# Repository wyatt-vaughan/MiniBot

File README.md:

# MiniBot

A swarm robotics platform built around autonomous chess. The system runs 34 small
differential-drive robots across an 8x8 board, each independently localized and
coordinated by a central Python application running on a Raspberry Pi.

The design is general-purpose — chess is the primary use case, but the platform
works for any scenario requiring coordinated movement of many small autonomous
robots in a bounded space.

Per-bot hardware cost is approximately $4 excluding PCB.

---

## Table of Contents

1. [System Architecture](#system-architecture)
2. [Hardware](#hardware)
3. [Communication Pathways](#communication-pathways)
4. [Server-Bot Sync](#server-bot-sync)
5. [Localization](#localization)
6. [PCB and CAD](#pcb-and-cad)
7. [Firmware](#firmware)

---

## System Architecture

The system has three layers:

**Coordinator** is a Python/PyQt6 application running on a Raspberry Pi. It holds
board state, runs path planning, drives the GUI, and sends motion commands to the
Server over USB serial.

**Server** is an ESP32 on the motherboard. It acts as a wireless gateway: it receives
CSV commands from the Coordinator over USB serial, translates them to binary ESP-NOW
messages, and broadcasts them to the bots. It also drives the electromagnets used for
localization and collects ACK/NACK responses back up to the Coordinator.

**MiniBots** are the robots themselves. Each runs an ESP32-C3 with five concurrent
FreeRTOS tasks handling motion control, wireless communication, position estimation,
and battery management entirely onboard.

---

## Hardware

### MiniBot

| Component | Details |
|-----------|---------|
| MCU | ESP32-C3 (RISC-V, 2.4 GHz WiFi) |
| Motors | 2x PMO8-2 miniature stepper motors |
| Motor drivers | STSPIN220 |
| Magnetometer | MMC5633NJL (I2C) |
| Power | ~170 mAh LiPo |
| Chassis | Fully 3D printed; 2x M2x5mm bolts, 2x 7mm ID o-rings for tires |
| PCB | Custom 4-layer; fits in the base of the chassis |

### Server / Motherboard

| Component | Details |
|-----------|---------|
| MCU | ESP32-C3 (RISC-V, 2.4 GHz WiFi) |
| Electromagnets | Multiple, positioned at fixed known coordinates on the board |
| Interface | USB serial to Raspberry Pi |
| WiFi | Soft AP; bots connect on a dedicated channel |

The electromagnets fire in a timed sequence that the MiniBots detect with their
onboard magnetometers. This is the primary localization mechanism.

---

## Communication Pathways

```mermaid
flowchart TD
    subgraph Coordinator["Coordinator (Raspberry Pi)"]
        GUI["GUI / Path Planner"]
        SH["SerialHandler\n(QThread)"]
        GUI -->|MoveCommand list| SH
    end

    subgraph Server["Server (Motherboard ESP32)"]
        ST["SerialTask"]
        CT["CommunicatorTask"]
        ET["ElectromagnetTask"]
        ST -->|CommandMessage| CT
        CT -->|GUIStatus| ST
    end

    subgraph Bots["MiniBot #1 ... #34 (ESP32-C3)"]
        COMM["EspNowCommunicator"]
        KIN["KinematicsController"]
        PE["PositionEstimator"]
        COMM -->|MotionCommand| KIN
        COMM -->|sync time| PE
    end

    SH -->|"Serial CSV Commands"| ST
    ST -->|"Serial CSV Responses"| SH
    CT -->|"ESP-NOW\nbroadcast / unicast Commands"| COMM
    COMM -->|"ESP-NOW unicast\nACK / NACK"| CT
    ET -.->|"electromagnetic\nframe pulses"| PE
```

### CSV Protocol (Host to Server)

All messages are prefixed with `>`. The Server parses these and forwards the
appropriate ESP-NOW message to the targeted bot(s).

| Type | Direction | Format |
|------|-----------|--------|
| 0 | Host to ESP32 | `>0,{id},{mode},{duty1},{duty2}` -- motor test |
| 1 | Host to ESP32 | `>1,{id},{x},{y},{theta_rad},{duration_ms}` -- position command |
| 2 | Host to ESP32 | `>2,{id}` -- position request |
| 3 | ESP32 to Host | `>3,{id},{x},{y},{theta_rad},{timestamp_ms},{battery_v}` -- ACK |
| 4 | ESP32 to Host | `>4,{id},{err_type},{timestamp_ms}` -- NACK |
| 5 | Host to ESP32 | `>5,{id}` -- mag field request |
| 6 | ESP32 to Host | `>6,{id},{bx},{by},{bz},{timestamp_ms}` -- mag field response |
| 7 | Host to ESP32 | `>7` -- sync broadcast |
| 254 | Host to ESP32 | `>254,{0 or 1}` -- electromagnet enable/disable |
| 255 | Both | `>255` -- ping/pong |

Theta is transmitted in radians on the wire. The Coordinator converts internally;
all application-level code uses degrees.

### ESP-NOW Protocol (Server to MiniBots)

Binary packed structs defined in `ESPNowMessages.h` (Server) and
`messages_espnow.h` (MiniBot). Key message types: `PositionCommand`,
`MotTestCommand`, `PositionRequest`, `PosSync`, `AckMessage`, `NackMessage`,
`MagneticFieldRequest`, `MagneticFieldResponse`.

---

## Server-Bot Sync

Before a localization measurement can be taken, every MiniBot needs to know
precisely when the electromagnet frame will begin so it can timestamp its
magnetometer samples against a common reference.

**Initiating a sync** is triggered by the Coordinator sending a `>7` sync command.
The Server's `CommunicatorTask` handles it as follows:

1. A `PosSyncCommand` is broadcast to all bots. The message includes a timeout
   indicating how long the bots should stay awake listening for the frame.
2. After a short delay, the Server sends a rapid burst of `PosSync` pulses. Each
   carries a `next_frame_us` field indicating how many microseconds until the
   electromagnet frame starts.
3. The `ElectromagnetTask` fires the frame immediately after the burst completes.

**On each MiniBot**, when `PosSyncCommand` is received, `EspNowCommunicator` sets
a deadline and raises `waiting_for_pos_sync`. The ESP-NOW receive callback captures
a high-resolution timestamp the instant each `PosSync` pulse arrives, before any
further processing. The task keeps only the earliest-arriving pulse from the burst —
minimum latency gives the best timing accuracy. The estimated frame start is
`receive_time + next_frame_us` from that best pulse.

Once the deadline passes, the bot calls `PositionEstimator_SetSyncTime()` with the
estimated frame-start, then sends an ACK with a small random delay to spread
simultaneous responses from many bots. If no pulse arrived in time, it sends
`ERR_SYNC_TIMEOUT`.

**Radio duty cycling** is tied to sync health. After a successful sync, each bot
enables duty cycling to save power. If sync becomes stale, the radio reverts to
always-on so the Server can reach the bot to re-establish sync.

---

## Localization

The Server fires each electromagnet in sequence as part of a repeating frame. Each
slot has a brief forward and reverse pulse to produce a detectable field, with a
known timing offset between slots.

On each MiniBot, `PositionEstimator_SensorTask` reads the magnetometer
continuously. Once a valid sync time is set, it timestamps each sample relative to
the frame start and assigns samples to their electromagnet slot by timing alone.

Once a complete frame is collected, `PositionEstimator_CalcTask` performs
trilateration using the field strength readings from the closest electromagnets and
their known board positions. This yields an (x, y, orientation) estimate with a
confidence score, which is used to weight a low-pass filter before the result is
committed to the robot's true pose via `robot.setTruePose()`.

---

## PCB and CAD

Current board designs are in `pcbs/`:

- `pcbs/MiniBot_MainBoard/` -- MiniBot PCB (ESP32-C3, stepper drivers, magnetometer, LiPo charger)
- `pcbs/Server_Motherboard/` -- Motherboard (ESP32-C3, electromagnet drivers, connectors)

Gerber files are in the `GERBERS/` subdirectory of each board folder.

CAD (OnShape):
https://cad.onshape.com/documents/4f8eaef75458146767928ab5/w/f159d6d65b9091531e1ead34/e/13b51722310f27710438c727

---

## Firmware

Each firmware project has its own README with task breakdowns, key objects, and
build instructions.

- `firmware/MiniBot_Coordinator/` -- Python/PyQt6 host application
- `firmware/MiniBot_Server/` -- ESP32 motherboard firmware (PlatformIO)
- `firmware/MiniBot_StepperClient/` -- ESP32-C3 per-bot firmware (PlatformIO)

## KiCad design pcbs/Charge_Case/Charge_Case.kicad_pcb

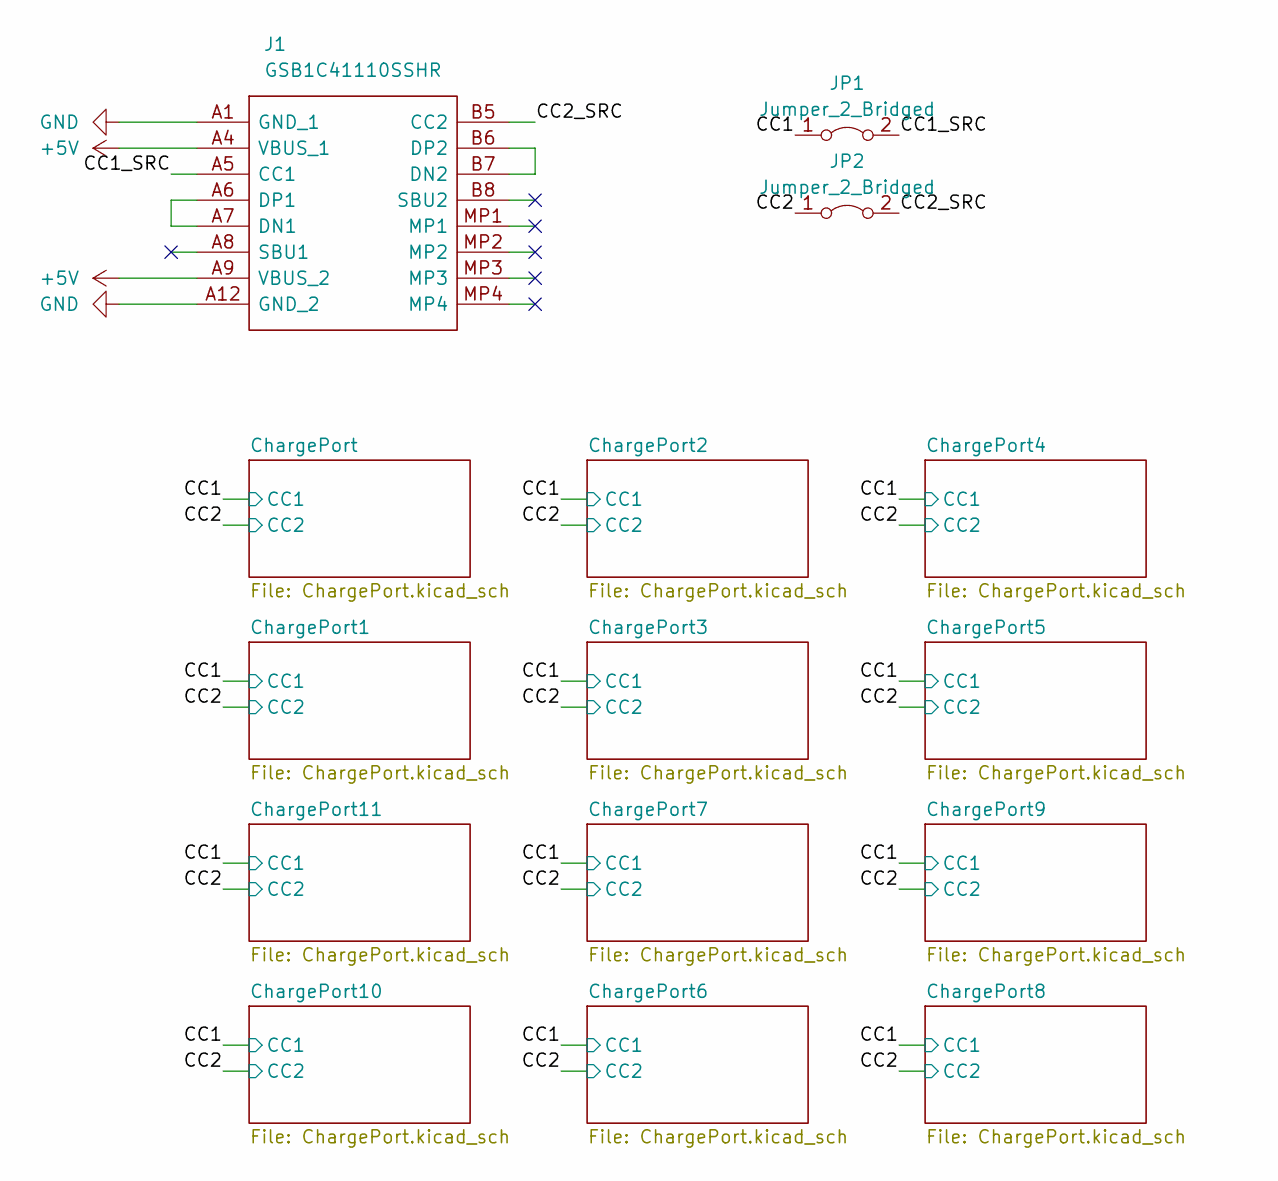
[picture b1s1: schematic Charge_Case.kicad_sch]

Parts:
J1: GSB1C41110SSHR; Manufacturer_Part_Number GSB1C41110SSHR
JP1, JP2: Jumper_2_Bridged; SolderJumper-2_P1.3mm_Bridged_RoundedPad1.0x1.5mm

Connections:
+5V: J1.A4 (VBUS_1), J1.A9 (VBUS_2); also elsewhere on the board
/CC1: JP1.1 (A); also elsewhere on the board
/CC1_SRC: J1.A5 (CC1), JP1.2 (B)
/CC2: JP2.1 (A); also elsewhere on the board
/CC2_SRC: J1.B5 (CC2), JP2.2 (B)
GND: J1.A1 (GND_1), J1.A12 (GND_2); also elsewhere on the board
unnamed: J1.A6 (DP1), J1.A7 (DN1)
unnamed: J1.B6 (DP2), J1.B7 (DN2)

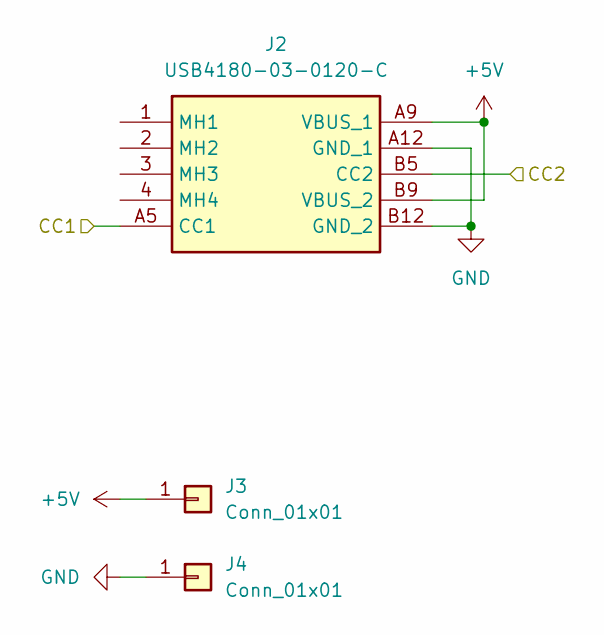
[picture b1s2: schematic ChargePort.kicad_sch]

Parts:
J2: USB4180-03-0120-C; USB4180030120C; Mouser Part Number 640-USB4180-03-0120C
J3, J4: Conn_01x01; TestPoint_THTPad_1.0x1.0mm_Drill0.5mm

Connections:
+5V: J2.A9 (VBUS_1), J2.B9 (VBUS_2), J3.1; also elsewhere on the board
/CC1: J2.A5 (CC1); also elsewhere on the board
/CC2: J2.B5 (CC2); also elsewhere on the board
GND: J2.A12 (GND_1), J2.B12 (GND_2), J4.1; also elsewhere on the board

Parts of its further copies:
J5, J8, J11, J14, J17, J20, J23, J26, J29, J32, J35: USB4180-03-0120-C; USB4180030120C; Mouser Part Number 640-USB4180-03-0120C
J6, J7, J9, J10, J12, J13, J15, J16, J18, J19, J21, J22, J24, J25, J27, J28, J30, J31, J33, J34, J36, J37: Conn_01x01; TestPoint_THTPad_1.0x1.0mm_Drill0.5mm

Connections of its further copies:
+5V: J5.A9 (VBUS_1), J5.B9 (VBUS_2), J6.1, J8.A9 (VBUS_1), J8.B9 (VBUS_2), J9.1, J11.A9 (VBUS_1), J11.B9 (VBUS_2), J12.1, J14.A9 (VBUS_1), J14.B9 (VBUS_2), J15.1, J17.A9 (VBUS_1), J17.B9 (VBUS_2), J18.1, J20.A9 (VBUS_1), J20.B9 (VBUS_2), J21.1, J23.A9 (VBUS_1), J23.B9 (VBUS_2), J24.1, J26.A9 (VBUS_1), J26.B9 (VBUS_2), J27.1, J29.A9 (VBUS_1), J29.B9 (VBUS_2), J30.1, J32.A9 (VBUS_1), J32.B9 (VBUS_2), J33.1, J35.A9 (VBUS_1), J35.B9 (VBUS_2), J36.1; also elsewhere on the board
/CC1: J5.A5 (CC1), J8.A5 (CC1), J11.A5 (CC1), J14.A5 (CC1), J17.A5 (CC1), J20.A5 (CC1), J23.A5 (CC1), J26.A5 (CC1), J29.A5 (CC1), J32.A5 (CC1), J35.A5 (CC1); also elsewhere on the board
/CC2: J5.B5 (CC2), J8.B5 (CC2), J11.B5 (CC2), J14.B5 (CC2), J17.B5 (CC2), J20.B5 (CC2), J23.B5 (CC2), J26.B5 (CC2), J29.B5 (CC2), J32.B5 (CC2), J35.B5 (CC2); also elsewhere on the board
GND: J5.A12 (GND_1), J5.B12 (GND_2), J7.1, J8.A12 (GND_1), J8.B12 (GND_2), J10.1, J11.A12 (GND_1), J11.B12 (GND_2), J13.1, J14.A12 (GND_1), J14.B12 (GND_2), J16.1, J17.A12 (GND_1), J17.B12 (GND_2), J19.1, J20.A12 (GND_1), J20.B12 (GND_2), J22.1, J23.A12 (GND_1), J23.B12 (GND_2), J25.1, J26.A12 (GND_1), J26.B12 (GND_2), J28.1, J29.A12 (GND_1), J29.B12 (GND_2), J31.1, J32.A12 (GND_1), J32.B12 (GND_2), J34.1, J35.A12 (GND_1), J35.B12 (GND_2), J37.1; also elsewhere on the board

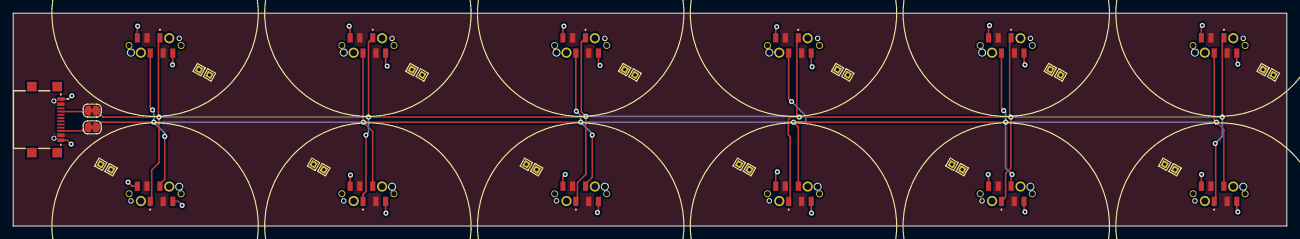
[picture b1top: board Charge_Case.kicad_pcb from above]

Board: 2 copper layers, 197.5 x 33.0 mm, 39 parts (0 on the bottom side), 8 nets.

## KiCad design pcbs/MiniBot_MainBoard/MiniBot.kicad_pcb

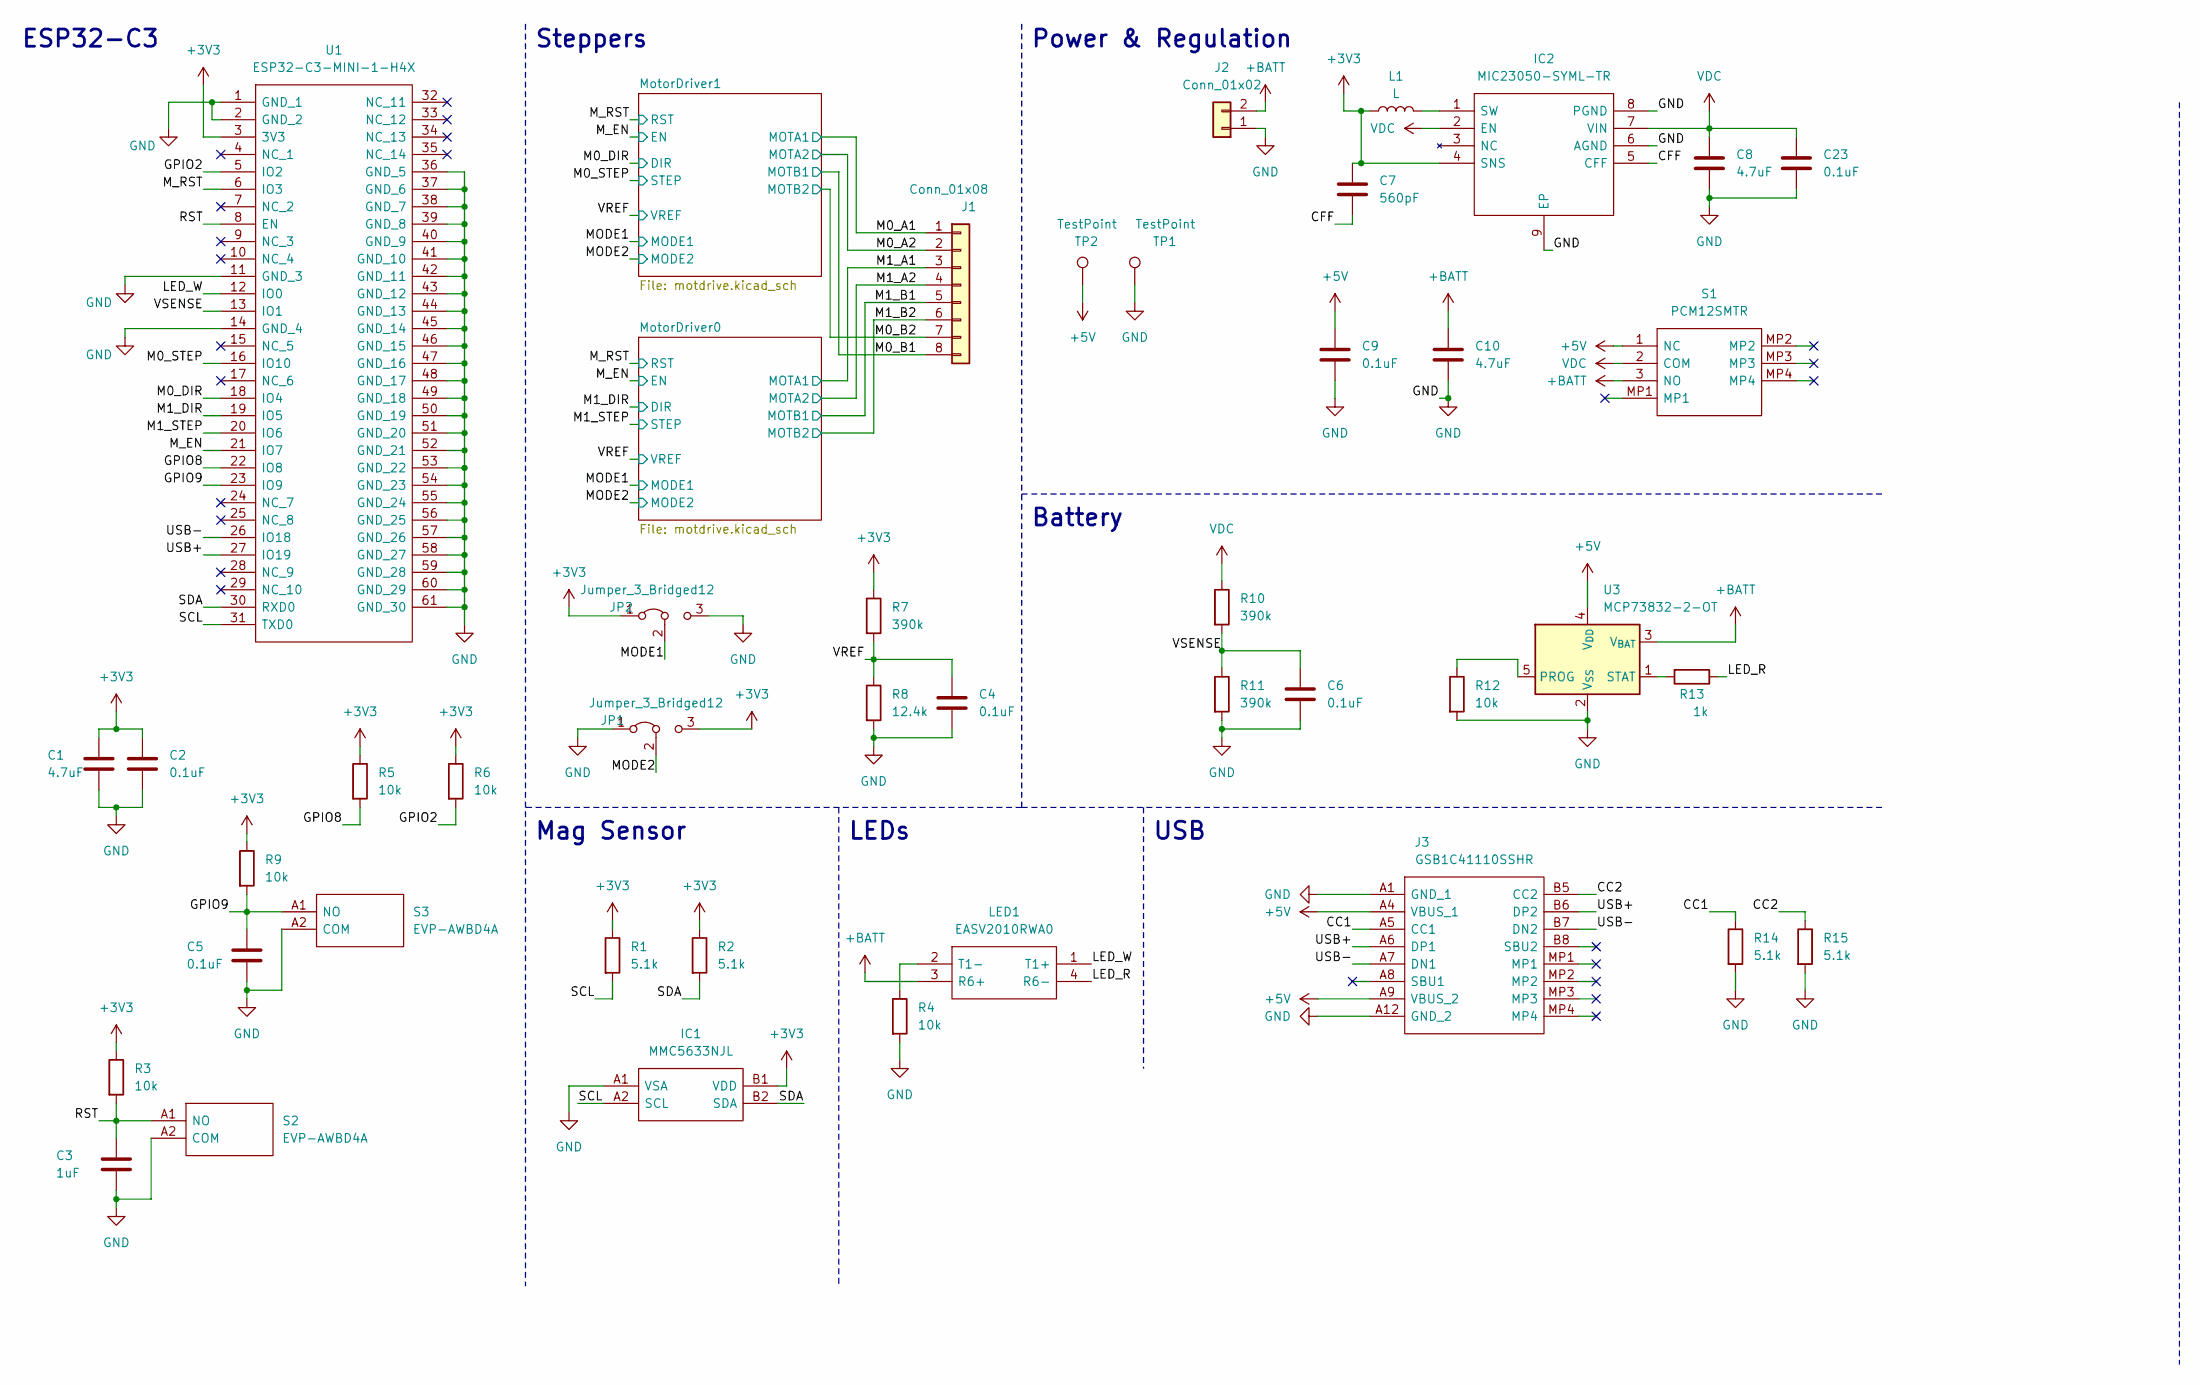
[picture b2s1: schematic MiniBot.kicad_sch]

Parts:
C1, C8, C10: 4.7uF; C_0402_1005Metric
C2, C4, C5, C6, C9, C23: 0.1uF; C_0402_1005Metric
C3: 1uF; C_0402_1005Metric
C7: 560pF; C_0402_1005Metric
IC1: MMC5633NJL; BGA4C40P2X2_85X85X60; Mouser Part Number 438-MMC5633NJL
IC2: MIC23050-SYML-TR; SON50P200X200X90-9N-D; Mouser Part Number 998-MIC23050-SYMLTR
J1: Conn_01x08; Molex_PicoBlade_53047-0810_1x08_P1.25mm_Vertical
J2: Conn_01x02; JST_PH_S2B-PH-K_1x02_P2.00mm_Horizontal
J3: GSB1C41110SSHR; Manufacturer_Part_Number GSB1C41110SSHR
JP1, JP2: Jumper_3_Bridged12; SolderJumper-3_P1.3mm_Bridged12_RoundedPad1.0x1.5mm
L1: L; L_0805_2012Metric
LED1: EASV2010RWA0; Mouser Part Number 638-EASV2010RWA0
R1, R2, R14, R15: 5.1k; R_0402_1005Metric
R3, R4, R5, R6, R9, R12: 10k; R_0402_1005Metric
R7, R10, R11: 390k; R_0402_1005Metric
R8: 12.4k; R_0402_1005Metric
R13: 1k; R_0402_1005Metric
S1: PCM12SMTR; Mouser Part Number 611-PCM12SMTR
S2, S3: EVP-AWBD4A; EVPAWBD4A; Mouser Part Number 667-EVP-AWBD4A
TP1, TP2: TestPoint; TestPoint_Pad_D1.0mm
U1: ESP32-C3-MINI-1-H4X; ESP32C3MINI1H4X; Mouser Part Number 356-ESP32C3MINI1H4X
U3: MCP73832-2-OT; SOT-23-5

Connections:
+3V3: C1.2, C2.1, C7.1, IC1.B1 (VDD), IC2.4 (SNS), JP1.3 (B), JP2.1 (A), L1.1, R1.1, R2.1, R3.1, R5.1, R6.1, R7.1, R9.1, U1.3 (3V3)
+5V: C9.1, J3.A4 (VBUS_1), J3.A9 (VBUS_2), S1.1 (NC), TP2.1, U3.4 (V_{DD})
+BATT: C10.1, J2.2, LED1.3 (R6+), S1.3 (NO), U3.3 (V_{BAT})
/CC1: J3.A5 (CC1), R14.1
/CC2: J3.B5 (CC2), R15.1
/CFF: C7.2, IC2.5 (CFF)
/GPIO2: R6.2, U1.5 (IO2)
/GPIO8: R5.2, U1.22 (IO8)
/GPIO9: C5.1, R9.2, S3.A1 (NO), U1.23 (IO9)
/LED_R: LED1.4 (R6-), R13.1
/LED_W: LED1.1 (T1+), U1.12 (IO0)
/M0_A1: J1.1; also elsewhere on the board
/M0_A2: J1.2; also elsewhere on the board
/M0_B1: J1.8; also elsewhere on the board
/M0_B2: J1.7; also elsewhere on the board
/M0_DIR: U1.18 (IO4); also elsewhere on the board
/M0_STEP: U1.16 (IO10); also elsewhere on the board
/M1_A1: J1.3; also elsewhere on the board
/M1_A2: J1.4; also elsewhere on the board
/M1_B1: J1.5; also elsewhere on the board
/M1_B2: J1.6; also elsewhere on the board
/M1_DIR: U1.19 (IO5); also elsewhere on the board
/M1_STEP: U1.20 (IO6); also elsewhere on the board
/MODE1: JP2.2 (C); also elsewhere on the board
/MODE2: JP1.2 (C); also elsewhere on the board
/M_EN: U1.21 (IO7); also elsewhere on the board
/M_RST: U1.6 (IO3); also elsewhere on the board
/RST: C3.1, R3.2, S2.A1 (NO), U1.8 (EN)
/SCL: IC1.A2 (SCL), R1.2, U1.31 (TXD0)
/SDA: IC1.B2 (SDA), R2.2, U1.30 (RXD0)
/USB+: J3.A6 (DP1), J3.B6 (DP2), U1.27 (IO19)
/USB-: J3.A7 (DN1), J3.B7 (DN2), U1.26 (IO18)
/VREF: C4.1, R7.2, R8.1; also elsewhere on the board
/VSENSE: C6.1, R10.2, R11.1, U1.13 (IO1)
GND: C1.1, C2.2, C3.2, C4.2, C5.2, C6.2, C8.2, C9.2, C10.2, C23.2, IC1.A1 (VSA), IC2.6 (AGND), IC2.8 (PGND), IC2.9 (EP), J2.1, J3.A1 (GND_1), J3.A12 (GND_2), JP1.1 (A), JP2.3 (B), R4.2, R8.2, R11.2, R12.2, R14.2, R15.2, S2.A2 (COM), S3.A2 (COM), TP1.1, U1.1 (GND_1), U1.2 (GND_2), U1.11 (GND_3), U1.14 (GND_4), U1.36 (GND_5), U1.37 (GND_6), U1.38 (GND_7), U1.39 (GND_8), U1.40 (GND_9), U1.41 (GND_10), U1.42 (GND_11), U1.43 (GND_12), U1.44 (GND_13), U1.45 (GND_14), U1.46 (GND_15), U1.47 (GND_16), U1.48 (GND_17), U1.49 (GND_18), U1.50 (GND_19), U1.51 (GND_20), U1.52 (GND_21), U1.53 (GND_22), U1.54 (GND_23), U1.55 (GND_24), U1.56 (GND_25), U1.57 (GND_26), U1.58 (GND_27), U1.59 (GND_28), U1.60 (GND_29), U1.61 (GND_30), U3.2 (V_{SS}); also elsewhere on the board
unnamed: IC2.1 (SW), L1.2
unnamed: LED1.2 (T1-), R4.1
unnamed: R12.1, U3.5 (PROG)
unnamed: R13.2, U3.1 (STAT)
VDC: C8.1, C23.1, IC2.2 (EN), IC2.7 (VIN), R10.1, S1.2 (COM); also elsewhere on the board

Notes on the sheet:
ESP32-C3
Power & Regulation
Battery
Mag Sensor
LEDs
USB
Steppers

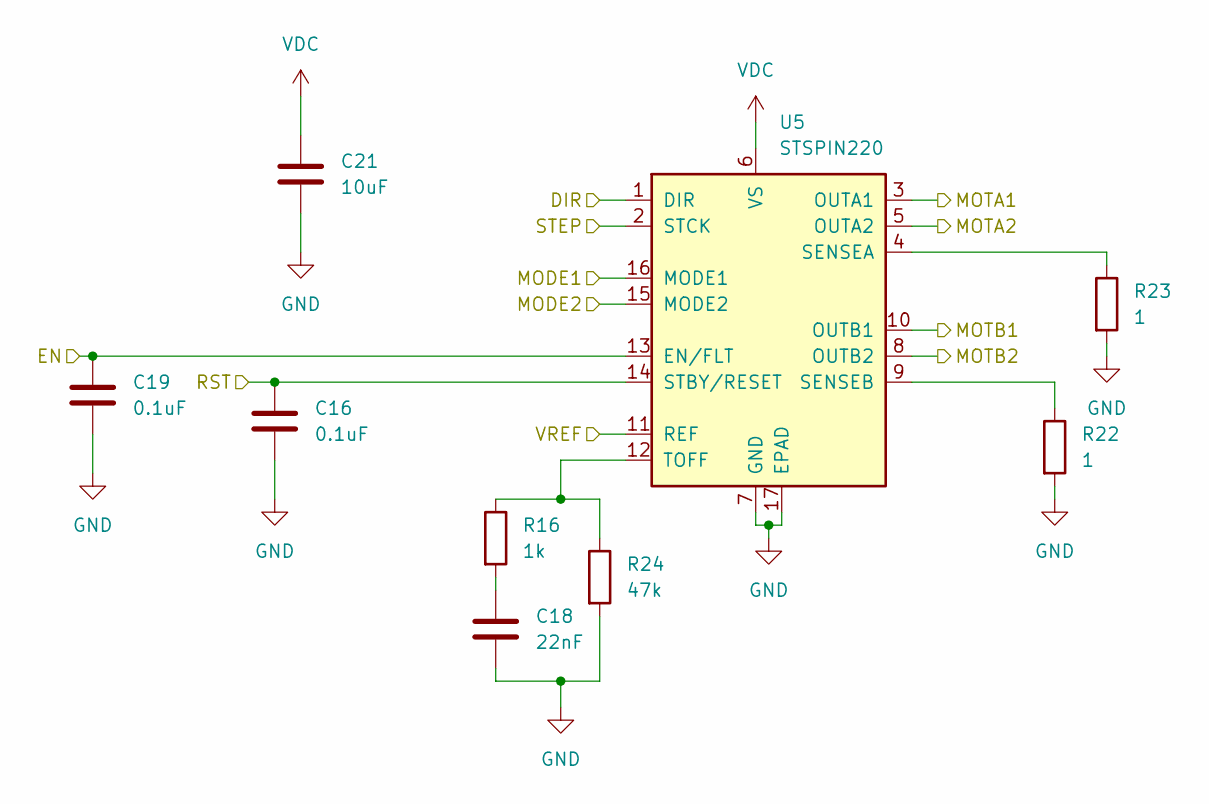
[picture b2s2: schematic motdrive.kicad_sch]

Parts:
C16, C19: 0.1uF; C_0402_1005Metric
C18: 22nF; C_0402_1005Metric
C21: 10uF; C_0402_1005Metric
R16: 1k; R_0402_1005Metric
R22, R23: 1; R_0402_1005Metric; Part Number AC0402FR-7W1RL
R24: 47k; R_0402_1005Metric
U5: STSPIN220; VQFN-16-1EP_3x3mm_P0.5mm_EP1.8x1.8mm

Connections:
/M1_A1: U5.3 (OUTA1); also elsewhere on the board
/M1_A2: U5.5 (OUTA2); also elsewhere on the board
/M1_B1: U5.10 (OUTB1); also elsewhere on the board
/M1_B2: U5.8 (OUTB2); also elsewhere on the board
/M1_DIR: U5.1 (DIR); also elsewhere on the board
/M1_STEP: U5.2 (STCK); also elsewhere on the board
/MODE1: U5.16 (MODE1); also elsewhere on the board
/MODE2: U5.15 (MODE2); also elsewhere on the board
/M_EN: C19.1, U5.13 (EN/FLT); also elsewhere on the board
/M_RST: C16.1, U5.14 (STBY/RESET); also elsewhere on the board
/VREF: U5.11 (REF); also elsewhere on the board
GND: C16.2, C18.2, C19.2, C21.2, R22.2, R23.2, R24.2, U5.7 (GND), U5.17 (EPAD); also elsewhere on the board
unnamed: C18.1, R16.2
unnamed: R23.1, U5.4 (SENSEA)
unnamed: R22.1, U5.9 (SENSEB)
VDC: C21.1, U5.6 (VS); also elsewhere on the board

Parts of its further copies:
C15, C20: 0.1uF; C_0402_1005Metric
C17: 10uF; C_0402_1005Metric
C22: 22nF; C_0402_1005Metric
R18, R19: 1; R_0402_1005Metric; Part Number AC0402FR-7W1RL
R20: 1k; R_0402_1005Metric
R25: 47k; R_0402_1005Metric
U4: STSPIN220; VQFN-16-1EP_3x3mm_P0.5mm_EP1.8x1.8mm

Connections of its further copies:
/M0_A1: U4.3 (OUTA1); also elsewhere on the board
/M0_A2: U4.5 (OUTA2); also elsewhere on the board
/M0_B1: U4.10 (OUTB1); also elsewhere on the board
/M0_B2: U4.8 (OUTB2); also elsewhere on the board
/M0_DIR: U4.1 (DIR); also elsewhere on the board
/M0_STEP: U4.2 (STCK); also elsewhere on the board
/MODE1: U4.16 (MODE1); also elsewhere on the board
/MODE2: U4.15 (MODE2); also elsewhere on the board
/M_EN: C15.1, U4.13 (EN/FLT); also elsewhere on the board
/M_RST: C20.1, U4.14 (STBY/RESET); also elsewhere on the board
/VREF: U4.11 (REF); also elsewhere on the board
GND: C15.2, C17.2, C20.2, C22.2, R18.2, R19.2, R25.2, U4.7 (GND), U4.17 (EPAD); also elsewhere on the board
unnamed: C22.1, R20.2
unnamed: R19.1, U4.4 (SENSEA)
unnamed: R18.1, U4.9 (SENSEB)
VDC: C17.1, U4.6 (VS); also elsewhere on the board

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
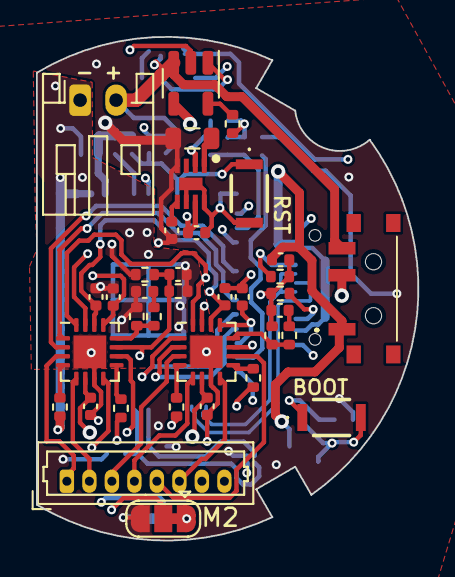
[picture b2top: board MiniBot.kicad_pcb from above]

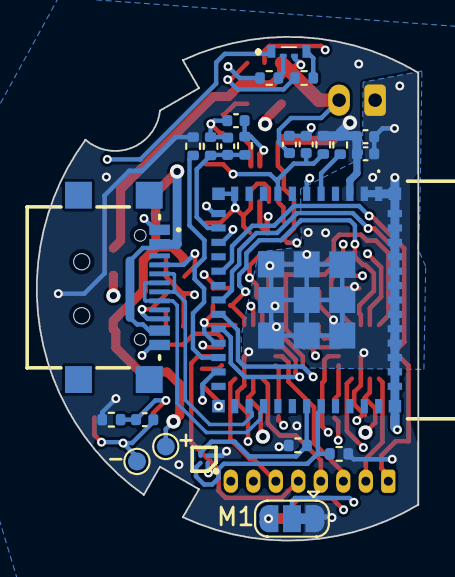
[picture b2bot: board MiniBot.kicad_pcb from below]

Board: 4 copper layers, 21.2 x 28.0 mm, 60 parts (24 on the bottom side), 48 nets.

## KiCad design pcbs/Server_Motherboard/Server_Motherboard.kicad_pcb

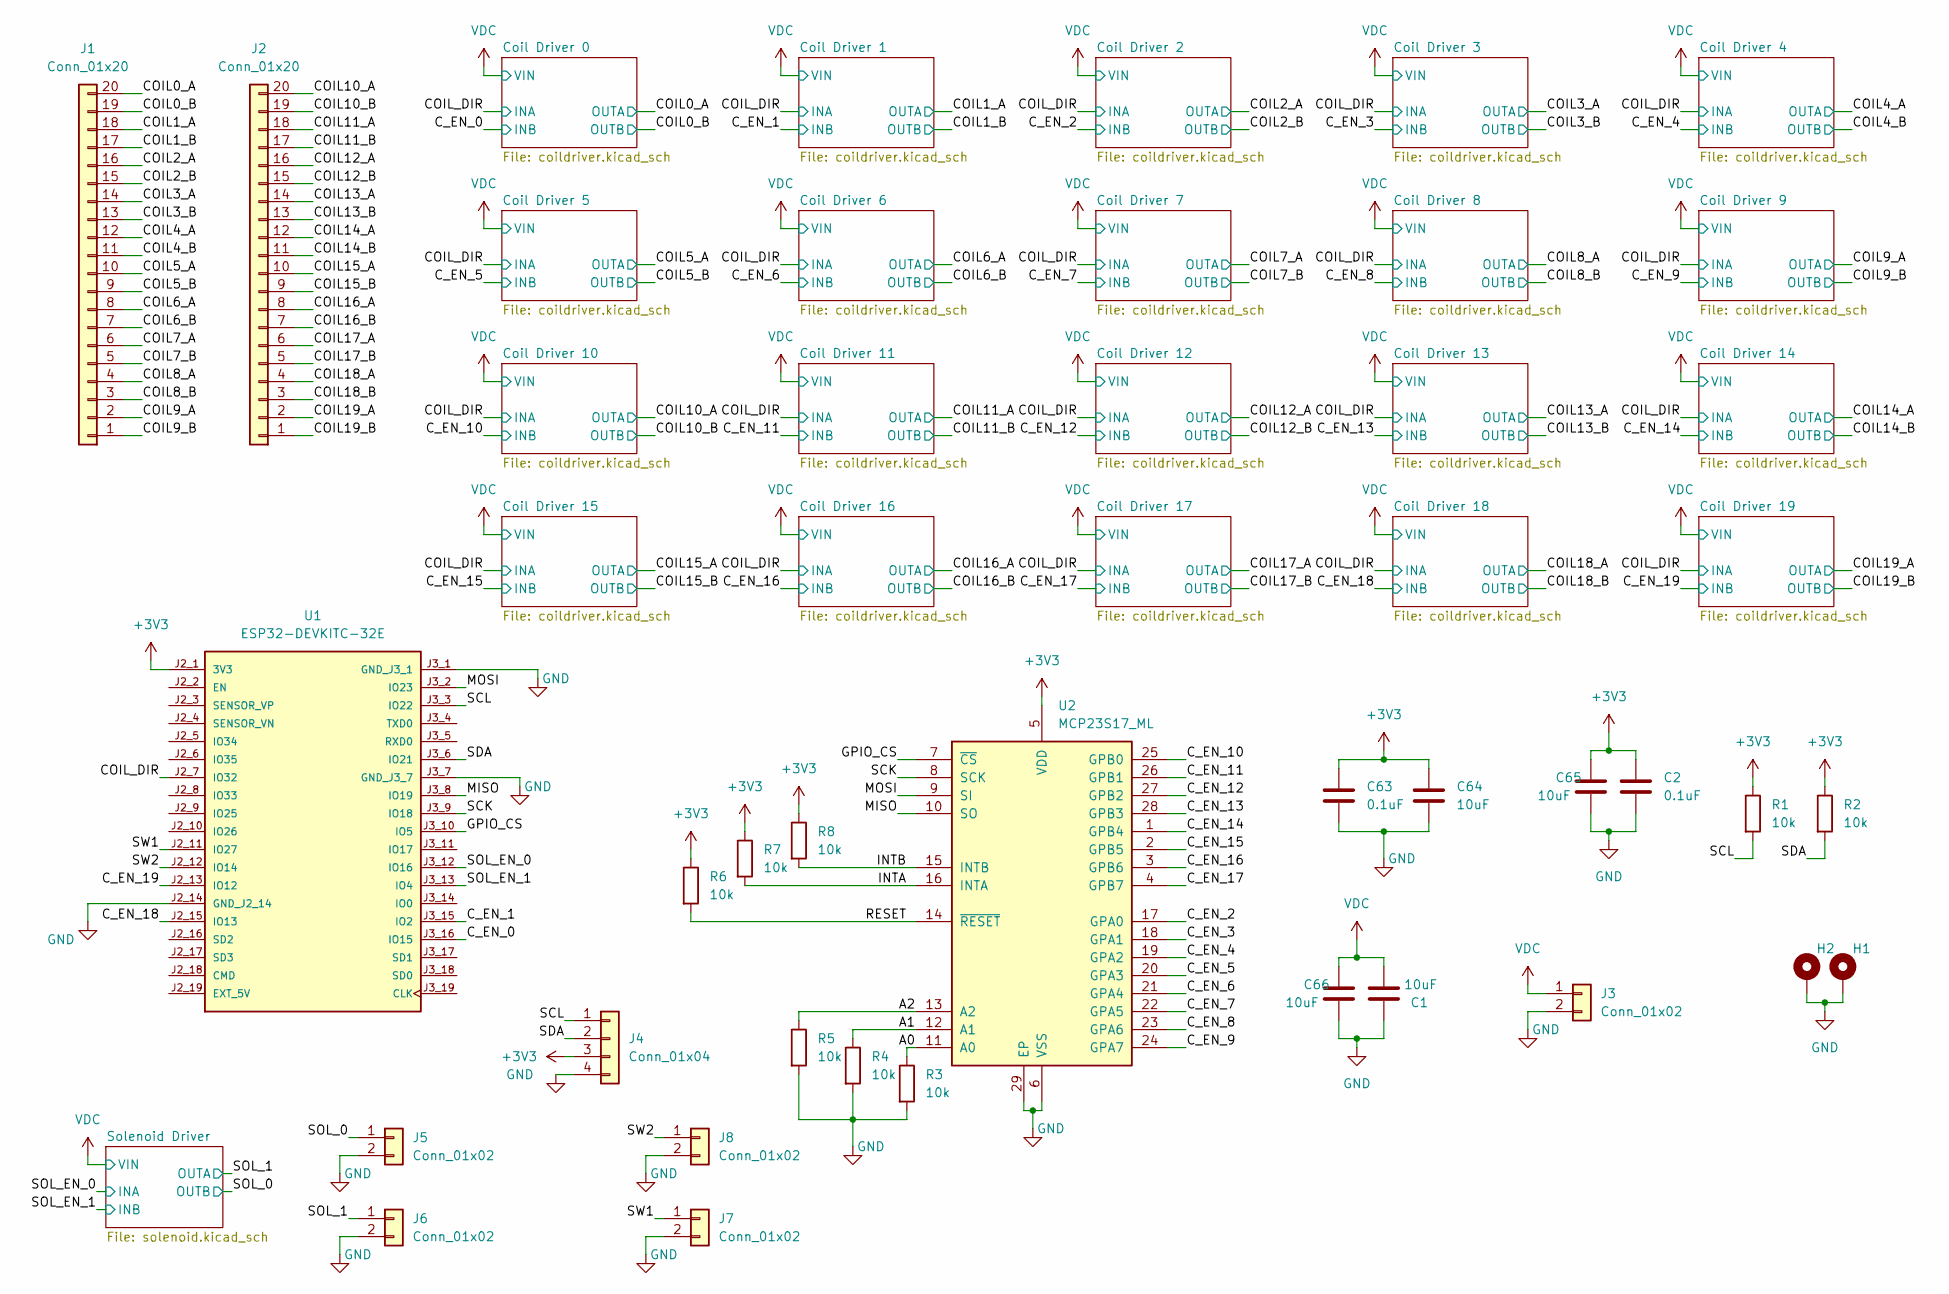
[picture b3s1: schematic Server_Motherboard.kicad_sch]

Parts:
C1, C64, C65, C66: 10uF; C_0603_1608Metric
C2, C63: 0.1uF; C_0402_1005Metric
H1, H2: MountingHole_Pad; MountingHole_2.7mm_M2.5_Pad_TopBottom
J1, J2: Conn_01x20; PinHeader_1x20_P2.00mm_Vertical
J3: Conn_01x02; PinHeader_1x02_P2.54mm_Vertical
J4: Conn_01x04; PinHeader_1x04_P2.54mm_Vertical
J5, J6, J7, J8: Conn_01x02; PinHeader_1x02_P2.54mm_Horizontal
R1, R2, R3, R4, R5, R6, R7, R8: 10k; R_0402_1005Metric
U1: ESP32-DEVKITC-32E; MODULE_ESP32-DEVKITC-32E; PARTREV 1.4
U2: MCP23S17_ML; QFN-28-1EP_6x6mm_P0.65mm_EP4.25x4.25mm

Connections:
+3V3: C2.1, C63.1, C64.1, C65.1, J4.3, R1.1, R2.1, R6.1, R7.1, R8.1, U1.J2_1 (3V3), U2.5 (VDD); also elsewhere on the board
/A0: R3.1, U2.11 (A0)
/A1: R4.1, U2.12 (A1)
/A2: R5.1, U2.13 (A2)
/COIL0_A: J1.20; also elsewhere on the board
/COIL0_B: J1.19; also elsewhere on the board
/COIL1_A: J1.18; also elsewhere on the board
/COIL1_B: J1.17; also elsewhere on the board
/COIL2_A: J1.16; also elsewhere on the board
/COIL2_B: J1.15; also elsewhere on the board
/COIL3_A: J1.14; also elsewhere on the board
/COIL3_B: J1.13; also elsewhere on the board
/COIL4_A: J1.12; also elsewhere on the board
/COIL4_B: J1.11; also elsewhere on the board
/COIL5_A: J1.10; also elsewhere on the board
/COIL5_B: J1.9; also elsewhere on the board
/COIL6_A: J1.8; also elsewhere on the board
/COIL6_B: J1.7; also elsewhere on the board
/COIL7_A: J1.6; also elsewhere on the board
/COIL7_B: J1.5; also elsewhere on the board
/COIL8_A: J1.4; also elsewhere on the board
/COIL8_B: J1.3; also elsewhere on the board
/COIL9_A: J1.2; also elsewhere on the board
/COIL9_B: J1.1; also elsewhere on the board
/COIL10_A: J2.20; also elsewhere on the board
/COIL10_B: J2.19; also elsewhere on the board
/COIL11_A: J2.18; also elsewhere on the board
/COIL11_B: J2.17; also elsewhere on the board
/COIL12_A: J2.16; also elsewhere on the board
/COIL12_B: J2.15; also elsewhere on the board
/COIL13_A: J2.14; also elsewhere on the board
/COIL13_B: J2.13; also elsewhere on the board
/COIL14_A: J2.12; also elsewhere on the board
/COIL14_B: J2.11; also elsewhere on the board
/COIL15_A: J2.10; also elsewhere on the board
/COIL15_B: J2.9; also elsewhere on the board
/COIL16_A: J2.8; also elsewhere on the board
/COIL16_B: J2.7; also elsewhere on the board
/COIL17_A: J2.6; also elsewhere on the board
/COIL17_B: J2.5; also elsewhere on the board
/COIL18_A: J2.4; also elsewhere on the board
/COIL18_B: J2.3; also elsewhere on the board
/COIL19_A: J2.2; also elsewhere on the board
/COIL19_B: J2.1; also elsewhere on the board
/COIL_DIR: U1.J2_7 (IO32); also elsewhere on the board
/C_EN_0: U1.J3_16 (IO15); also elsewhere on the board
/C_EN_1: U1.J3_15 (IO2); also elsewhere on the board
/C_EN_2: U2.17 (GPA0); also elsewhere on the board
/C_EN_3: U2.18 (GPA1); also elsewhere on the board
/C_EN_4: U2.19 (GPA2); also elsewhere on the board
/C_EN_5: U2.20 (GPA3); also elsewhere on the board
/C_EN_6: U2.21 (GPA4); also elsewhere on the board
/C_EN_7: U2.22 (GPA5); also elsewhere on the board
/C_EN_8: U2.23 (GPA6); also elsewhere on the board
/C_EN_9: U2.24 (GPA7); also elsewhere on the board
/C_EN_10: U2.25 (GPB0); also elsewhere on the board
/C_EN_11: U2.26 (GPB1); also elsewhere on the board
/C_EN_12: U2.27 (GPB2); also elsewhere on the board
/C_EN_13: U2.28 (GPB3); also elsewhere on the board
/C_EN_14: U2.1 (GPB4); also elsewhere on the board
/C_EN_15: U2.2 (GPB5); also elsewhere on the board
/C_EN_16: U2.3 (GPB6); also elsewhere on the board
/C_EN_17: U2.4 (GPB7); also elsewhere on the board
/C_EN_18: U1.J2_15 (IO13); also elsewhere on the board
/C_EN_19: U1.J2_13 (IO12); also elsewhere on the board
/GPIO_CS: U1.J3_10 (IO5), U2.7 (~CS)
/INTA: R7.2, U2.16 (INTA)
/INTB: R8.2, U2.15 (INTB)
/MISO: U1.J3_8 (IO19), U2.10 (SO)
/MOSI: U1.J3_2 (IO23), U2.9 (SI)
/RESET: R6.2, U2.14 (~RESET)
/SCK: U1.J3_9 (IO18), U2.8 (SCK)
/SCL: J4.1, R1.2, U1.J3_3 (IO22)
/SDA: J4.2, R2.2, U1.J3_6 (IO21)
/SOL_0: J5.1; also elsewhere on the board
/SOL_1: J6.1; also elsewhere on the board
/SOL_EN_0: U1.J3_12 (IO16); also elsewhere on the board
/SOL_EN_1: U1.J3_13 (IO4); also elsewhere on the board
/SW1: J7.1, U1.J2_11 (IO27)
/SW2: J8.1, U1.J2_12 (IO14)
GND: C1.1, C2.2, C63.2, C64.2, C65.2, C66.2, H1.1, H2.1, J3.2, J4.4, J5.2, J6.2, J7.2, J8.2, R3.2, R4.2, R5.2, U1.J2_14 (GND_J2_14), U1.J3_1 (GND_J3_1), U1.J3_7 (GND_J3_7), U2.6 (VSS), U2.29 (EP); also elsewhere on the board
VDC: C1.2, C66.1, J3.1; also elsewhere on the board
